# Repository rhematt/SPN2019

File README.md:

# SPN2019
Files related to PhD dissertation "Unified theory of Sensor Pattern Noise"

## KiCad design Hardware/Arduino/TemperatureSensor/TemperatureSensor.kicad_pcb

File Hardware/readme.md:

This folder contains the hardware components of this project.

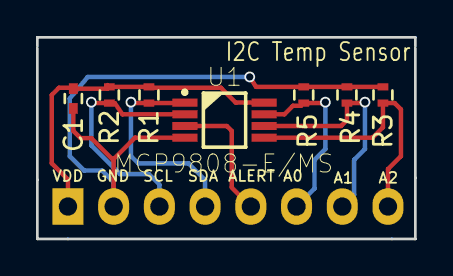
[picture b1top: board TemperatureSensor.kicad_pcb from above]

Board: 2 copper layers, 21.0 x 11.2 mm, 8 parts (1 on the bottom side), 8 nets.

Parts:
C1: 1uF; C_0402
P1: CONN_01X08; Pin_Header_Angled_1x08
R1, R2, R3, R4, R5: 10K; R_0402
U1: MCP9808-E/MS; SOP65P490X110-8N

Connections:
A0: P1.6, R5.2, U1.7
A1: P1.7, R4.2, U1.6
A2: P1.8, R3.2, U1.5
ALERT: P1.5, U1.3
GND: C1.2, P1.2, R3.1, R4.1, R5.1, U1.4
SCL: P1.3, R2.2, U1.2
SDA: P1.4, R1.2, U1.1
VDD: C1.1, P1.1, R1.1, R2.1, U1.8

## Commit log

2023-01-15 Moved FIles
2023-07-04 Create placeholder
